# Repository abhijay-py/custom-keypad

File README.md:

# custom-keypad
Utilized KiCAD and STM32Cube to design a keypad pre-programmed with 6 specific key bindings and a volume knob. <br>
Powered by a STM32H7A3RGT6 microcontroller with Cherry MX Brown Switches and a knurled metal volume knob. <br>
Enclosed the PCB with a custom black 3D printed case to improve the appearance, saftey, and stabliity of the device. 

Used consumer and keypad hardware interface device reports to create a custom HID report that was able to send both media and regular keyboard commands to PCs. 
Created a decoder + EXTI interrupt system to properly debounce and evaluate transistions in the rotary encoder to effectively adjust volume corresponding to the end user's turning of the dial. <br>

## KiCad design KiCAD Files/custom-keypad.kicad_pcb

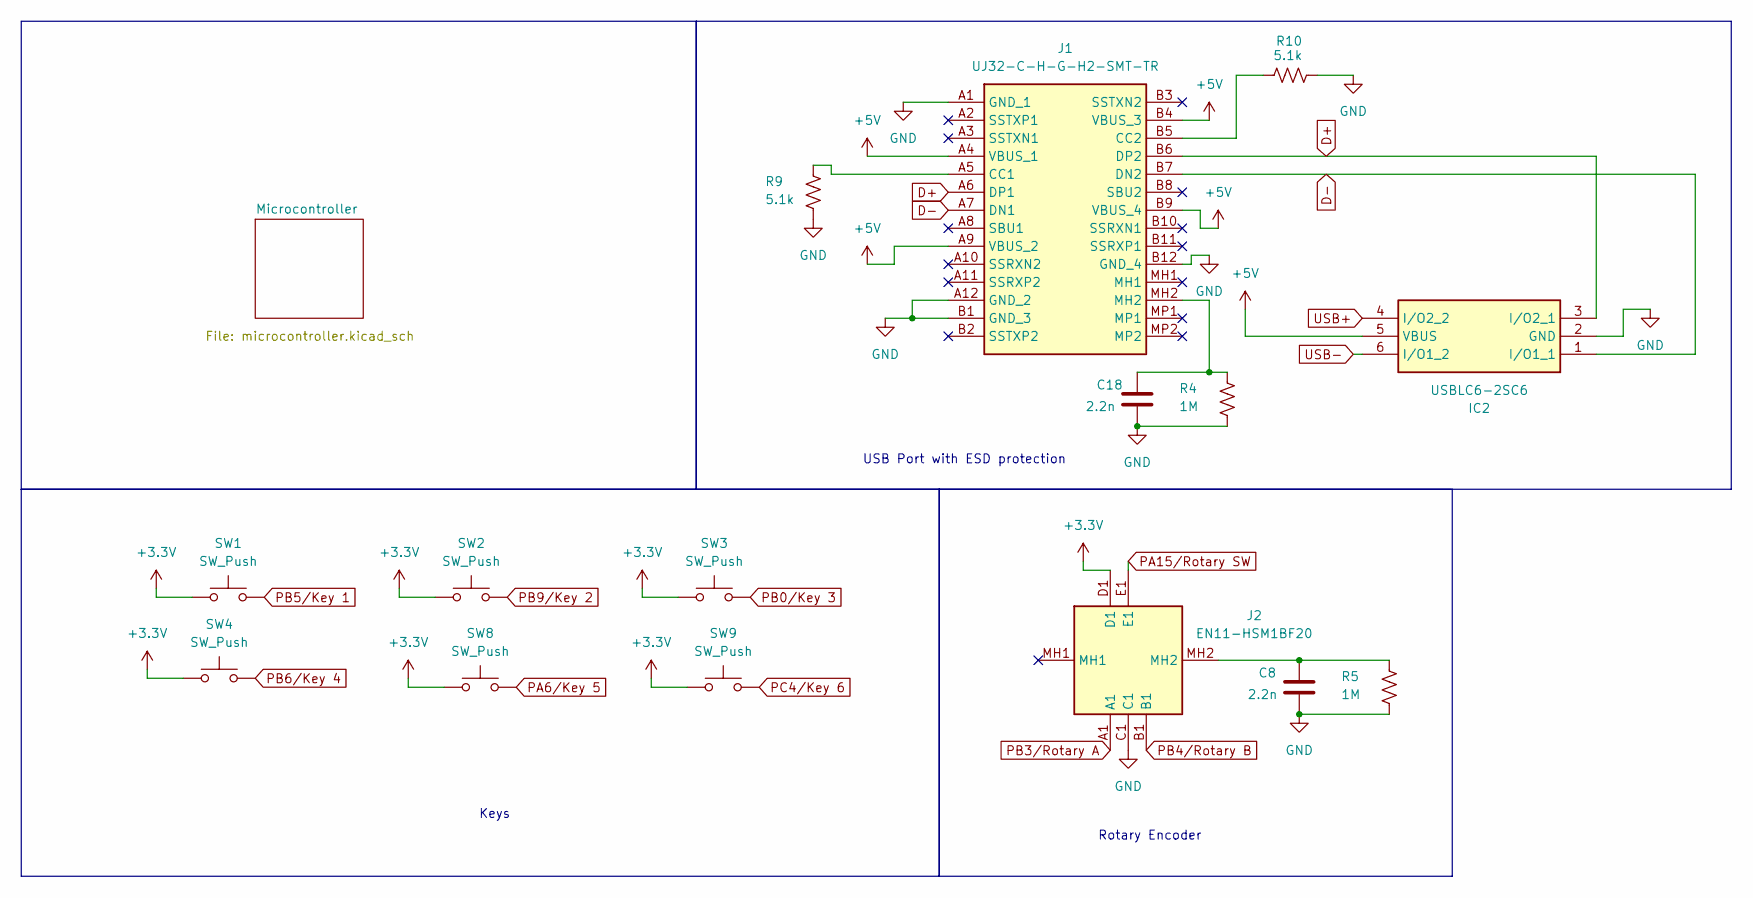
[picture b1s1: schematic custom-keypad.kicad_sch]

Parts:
C8, C18: 2.2n; C_0805_2012Metric_Pad1.18x1.45mm_HandSolder
IC2: USBLC6-2SC6; SOT95P280X145-6N; Mouser Part Number 511-USBLC6-2SC6
J1: UJ32-C-H-G-H2-SMT-TR; UJ32CHGH2SMTTR; Mouser Part Number 179-UJ32CHGH2SMTTR
J2: EN11-HSM1BF20; EN11HSM1BF20; Mouser Part Number 858-EN11-HSM1BF20
R4, R5: 1M; R_0805_2012Metric_Pad1.20x1.40mm_HandSolder
R9, R10: 5.1k; R_0805_2012Metric_Pad1.20x1.40mm_HandSolder
SW1, SW2, SW3, SW4, SW8, SW9: SW_Push; SW_MX

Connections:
+5V: IC2.5 (VBUS), J1.A4 (VBUS_1), J1.A9 (VBUS_2), J1.B4 (VBUS_3), J1.B9 (VBUS_4); also elsewhere on the board
D+: IC2.3 (I/O2_1), J1.A6 (DP1), J1.B6 (DP2)
D-: IC2.1 (I/O1_1), J1.A7 (DN1), J1.B7 (DN2)
GND: C8.2, C18.2, IC2.2 (GND), J1.A1 (GND_1), J1.A12 (GND_2), J1.B1 (GND_3), J1.B12 (GND_4), J2.C1, R4.2, R5.2, R9.2, R10.2; also elsewhere on the board
unnamed: C8.1, J2.MH2, R5.1
unnamed: C18.1, J1.MH2, R4.1
unnamed: J1.A5 (CC1), R9.1
unnamed: J1.B5 (CC2), R10.1
PA6/Key 5: SW8.2; also elsewhere on the board
PA15/Rotary SW: J2.E1; also elsewhere on the board
PB0/Key 3: SW3.2; also elsewhere on the board
PB3/Rotary A: J2.A1; also elsewhere on the board
PB4/Rotary B: J2.B1; also elsewhere on the board
PB5/Key 1: SW1.2; also elsewhere on the board
PB6/Key 4: SW4.2; also elsewhere on the board
PB9/Key 2: SW2.2; also elsewhere on the board
PC4/Key 6: SW9.2; also elsewhere on the board
USB+: IC2.4 (I/O2_2); also elsewhere on the board
USB-: IC2.6 (I/O1_2); also elsewhere on the board
VBAT: J2.D1, SW1.1, SW2.1, SW3.1, SW4.1, SW8.1, SW9.1; also elsewhere on the board

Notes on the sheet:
Keys
Rotary Encoder
USB Port with ESD protection

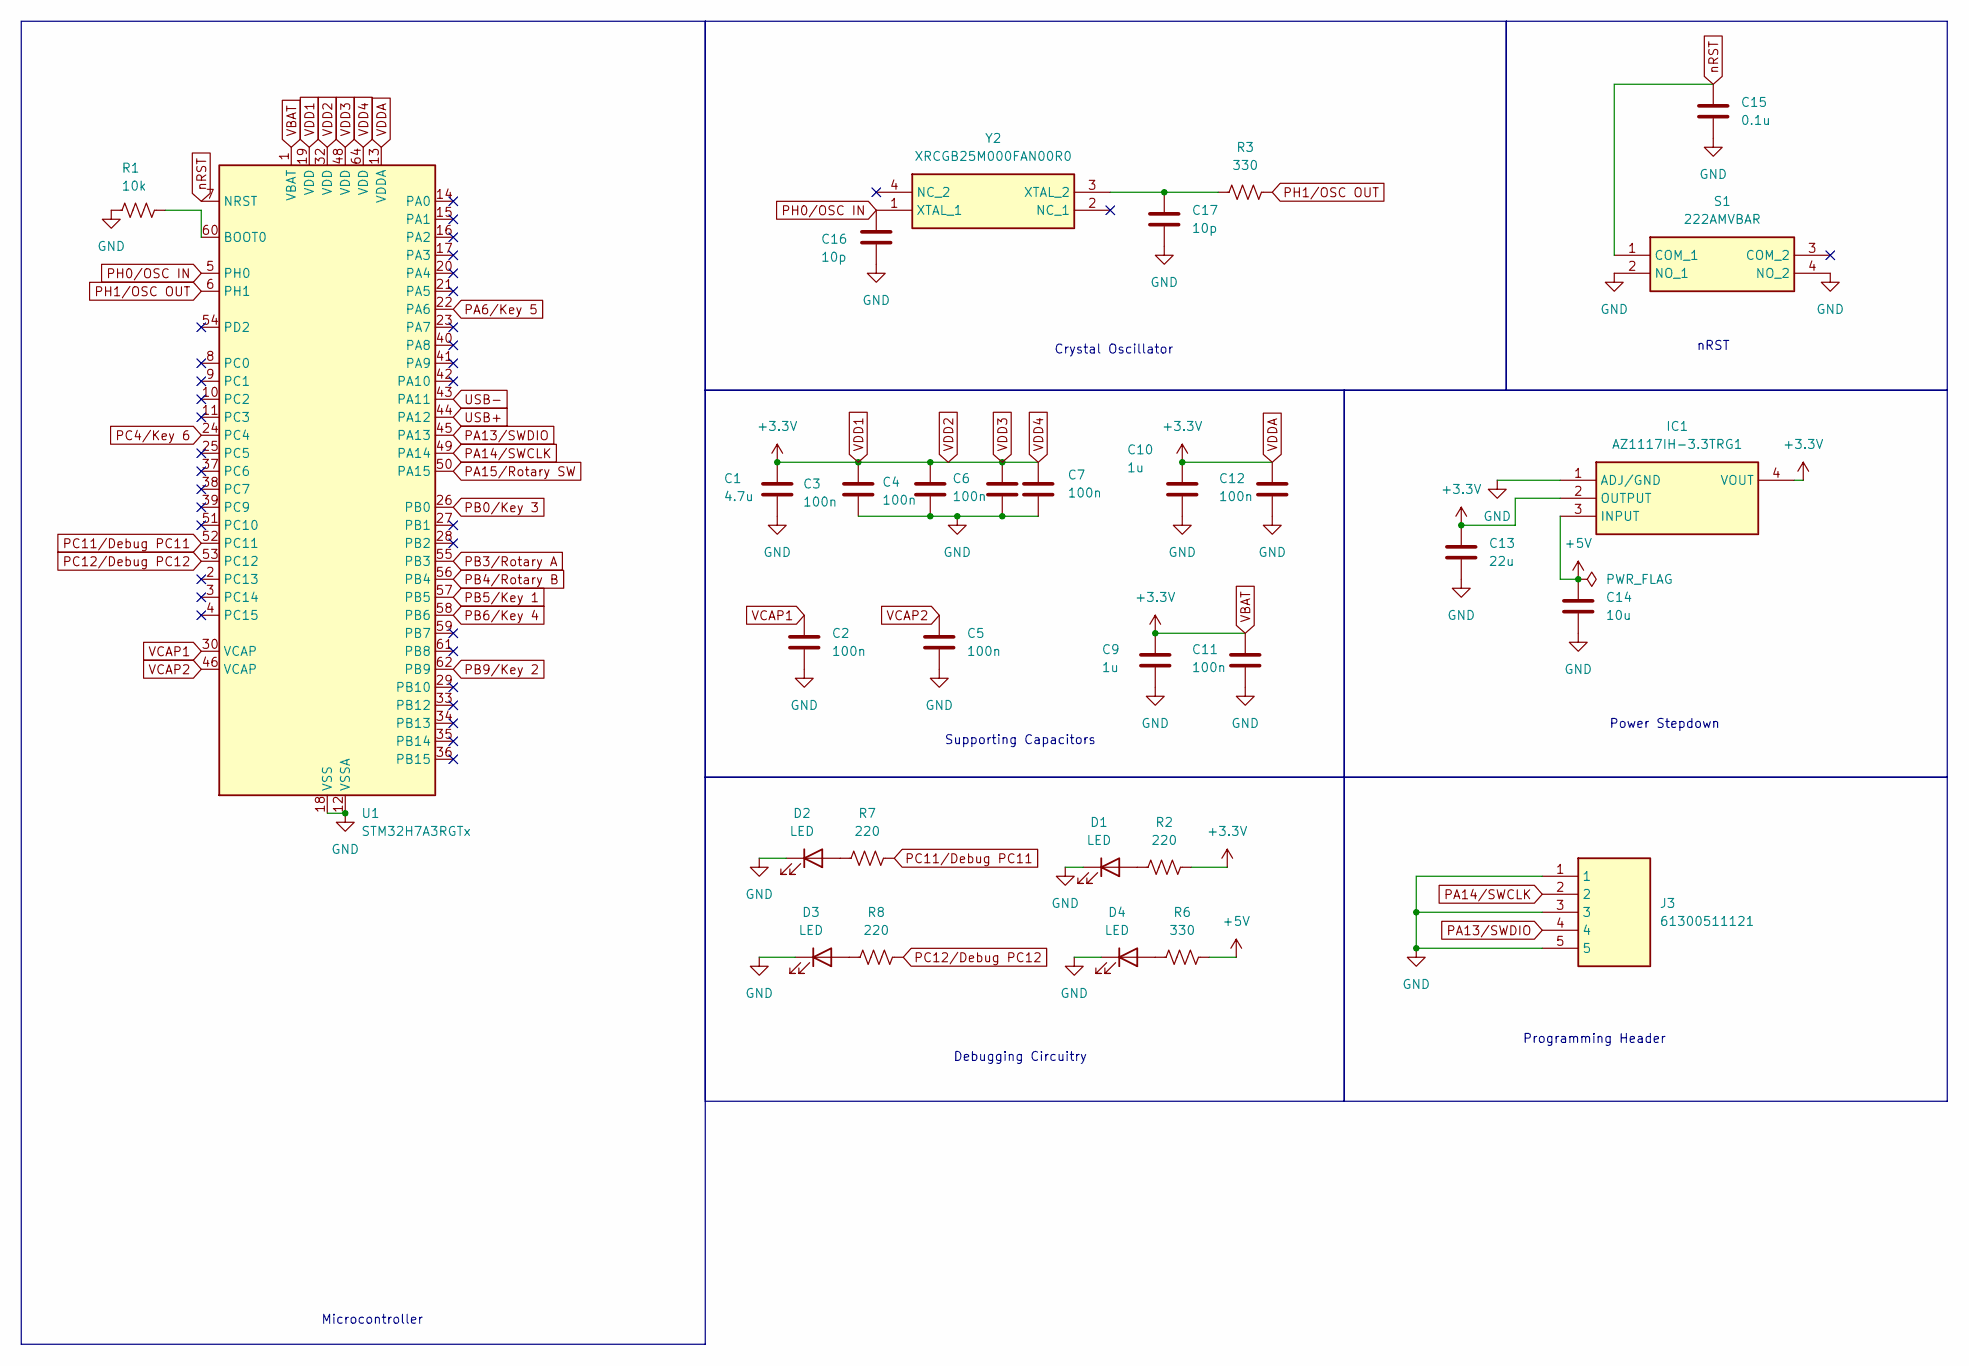
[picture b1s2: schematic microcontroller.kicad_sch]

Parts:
C1: 4.7u; C_0805_2012Metric_Pad1.18x1.45mm_HandSolder
C2, C3, C4, C5, C6, C7, C11, C12: 100n; C_0805_2012Metric_Pad1.18x1.45mm_HandSolder
C9, C10: 1u; C_0805_2012Metric_Pad1.18x1.45mm_HandSolder
C13: 22u; C_0805_2012Metric_Pad1.18x1.45mm_HandSolder
C14: 10u; C_0805_2012Metric_Pad1.18x1.45mm_HandSolder
C15: 0.1u; C_0805_2012Metric_Pad1.18x1.45mm_HandSolder
C16, C17: 10p; C_0805_2012Metric_Pad1.18x1.45mm_HandSolder
D1, D2, D3, D4: LED; LED_0805_2012Metric_Pad1.15x1.40mm_HandSolder
IC1: AZ1117IH-3.3TRG1; SOT230P700X180-4N; Mouser Part Number 621-AZ1117IH-3.3TRG1
J3: 61300511121; HDRV5W64P0X254_1X5_1270X254X854P; Mouser Part Number 710-61300511121
R1: 10k; R_0805_2012Metric_Pad1.20x1.40mm_HandSolder
R2, R7, R8: 220; R_0805_2012Metric_Pad1.20x1.40mm_HandSolder
R3, R6: 330; R_0805_2012Metric_Pad1.20x1.40mm_HandSolder
S1: 222AMVBAR; Mouser Part Number 774-222AMVBAR
U1: STM32H7A3RGTx; LQFP-64_10x10mm_P0.5mm
Y2: XRCGB25M000FAN00R0; XRCGB; Mouser Part Number 81-XRCGB25M000FAN0R0

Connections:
+5V: C14.1, IC1.3 (INPUT), R6.1; also elsewhere on the board
GND: C1.2, C2.2, C3.2, C4.2, C5.2, C6.2, C7.2, C9.2, C10.2, C11.2, C12.2, C13.2, C14.2, C15.2, C16.2, C17.2, D1.1 (K), D2.1 (K), D3.1 (K), D4.1 (K), IC1.1 (ADJ/GND), J3.1, J3.3, J3.5, R1.2, S1.2 (NO_1), S1.4 (NO_2), U1.12 (VSSA), U1.18 (VSS), U1.31 (VSS), U1.47 (VSS), U1.63 (VSS); also elsewhere on the board
unnamed: D1.2 (A), R2.2
unnamed: D2.2 (A), R7.2
unnamed: D3.2 (A), R8.2
unnamed: D4.2 (A), R6.2
unnamed: R1.1, U1.60 (BOOT0)
unnamed: C17.1, R3.1, Y2.3 (XTAL_2)
PA6/Key 5: U1.22 (PA6); also elsewhere on the board
PA13/SWDIO: J3.4, U1.45 (PA13)
PA14/SWCLK: J3.2, U1.49 (PA14)
PA15/Rotary SW: U1.50 (PA15); also elsewhere on the board
PB0/Key 3: U1.26 (PB0); also elsewhere on the board
PB3/Rotary A: U1.55 (PB3); also elsewhere on the board
PB4/Rotary B: U1.56 (PB4); also elsewhere on the board
PB5/Key 1: U1.57 (PB5); also elsewhere on the board
PB6/Key 4: U1.58 (PB6); also elsewhere on the board
PB9/Key 2: U1.62 (PB9); also elsewhere on the board
PC4/Key 6: U1.24 (PC4); also elsewhere on the board
PC11/Debug PC11: R7.1, U1.52 (PC11)
PC12/Debug PC12: R8.1, U1.53 (PC12)
PH0/OSC IN: C16.1, U1.5 (PH0), Y2.1 (XTAL_1)
PH1/OSC OUT: R3.2, U1.6 (PH1)
USB+: U1.44 (PA12); also elsewhere on the board
USB-: U1.43 (PA11); also elsewhere on the board
VBAT: C1.1, C3.1, C4.1, C6.1, C7.1, C9.1, C10.1, C11.1, C12.1, C13.1, IC1.2 (OUTPUT), IC1.4 (VOUT), R2.1, U1.1 (VBAT), U1.13 (VDDA), U1.19 (VDD), U1.32 (VDD), U1.48 (VDD), U1.64 (VDD); also elsewhere on the board
VCAP1: C2.1, U1.30 (VCAP)
VCAP2: C5.1, U1.46 (VCAP)
nRST: C15.1, S1.1 (COM_1), U1.7 (NRST)

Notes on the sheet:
Power Stepdown
Debugging Circuitry
nRST
Programming Header
Crystal Oscillator
Microcontroller
Supporting Capacitors

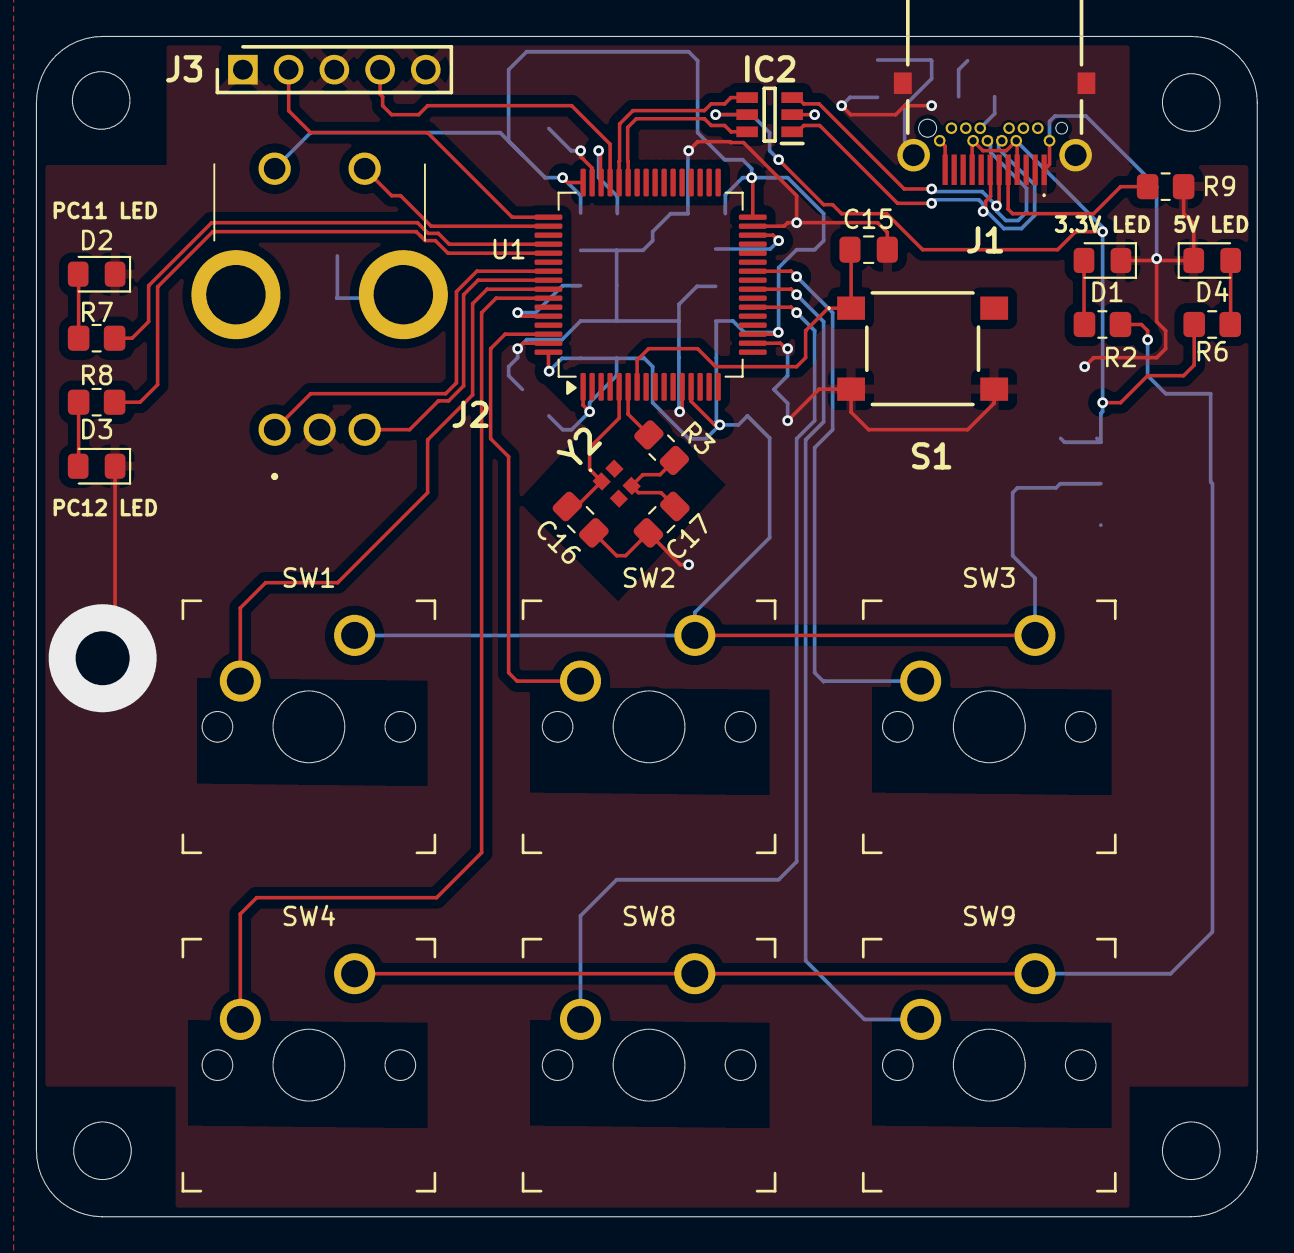
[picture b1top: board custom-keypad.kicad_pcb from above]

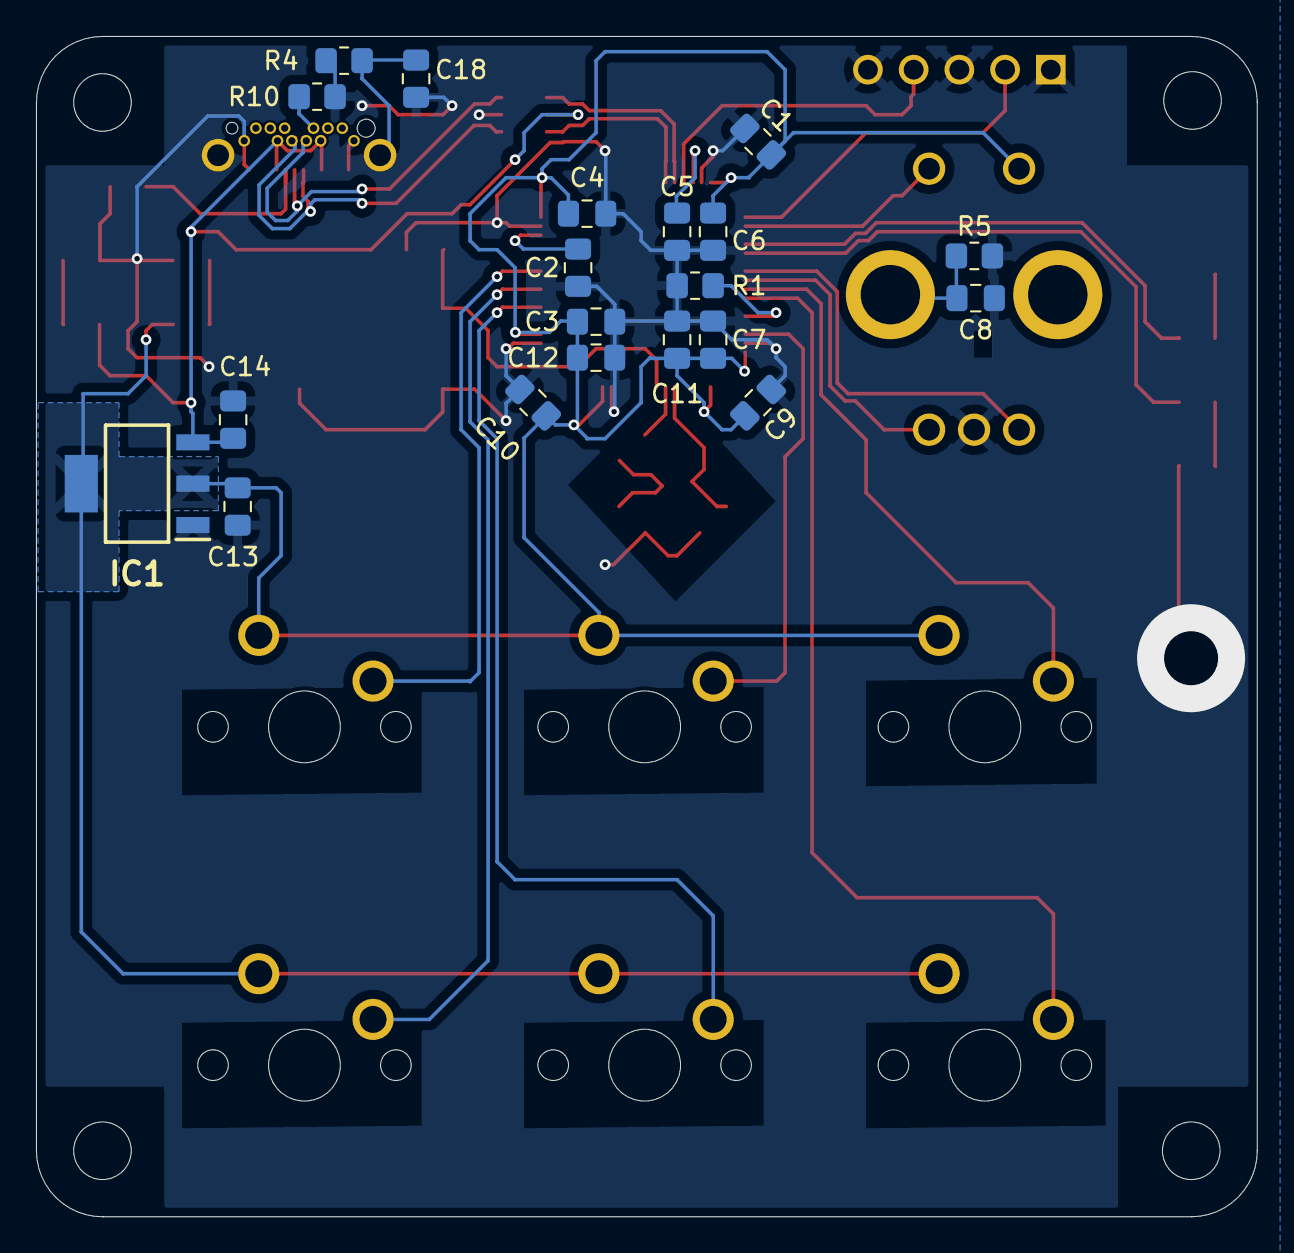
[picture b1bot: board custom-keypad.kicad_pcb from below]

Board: 2 copper layers, 67.8 x 65.6 mm, 46 parts (20 on the bottom side), 35 nets.

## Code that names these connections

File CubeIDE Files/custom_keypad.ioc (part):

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Mcu.Name=STM32H7A3R(G-I)Tx
Mcu.Package=LQFP64
Mcu.UserName=STM32H7A3RGTx
PA11.Mode=Device_Only_FS
PA11.Signal=USB_OTG_HS_DM
PA12.Mode=Device_Only_FS
PA12.Signal=USB_OTG_HS_DP
PA13.Mode=Serial_Wire
PA13.Signal=DEBUG_JTMS-SWDIO
PA14.Mode=Serial_Wire
PA14.Signal=DEBUG_JTCK-SWCLK
PA15.GPIOParameters=GPIO_PuPd
PA15.GPIO_PuPd=GPIO_PULLDOWN
PA15.Signal=GPIO_Input
PA6.GPIOParameters=GPIO_PuPd
PA6.GPIO_PuPd=GPIO_PULLDOWN
PA6.Signal=GPIO_Input
PB0.GPIOParameters=GPIO_PuPd
PB0.GPIO_PuPd=GPIO_PULLDOWN
PB0.Signal=GPIO_Input
PB3.GPIOParameters=GPIO_PuPd,GPIO_ModeDefaultEXTI
PB3.GPIO_ModeDefaultEXTI=GPIO_MODE_IT_RISING_FALLING
PB3.GPIO_PuPd=GPIO_PULLUP
PB3.Signal=GPXTI3
PB4.GPIOParameters=GPIO_PuPd,GPIO_ModeDefaultEXTI
PB4.GPIO_ModeDefaultEXTI=GPIO_MODE_IT_RISING_FALLING
PB4.GPIO_PuPd=GPIO_PULLUP
PB4.Signal=GPXTI4
PB5.GPIOParameters=GPIO_PuPd
PB5.GPIO_PuPd=GPIO_PULLDOWN
PB5.Signal=GPIO_Input
PB6.GPIOParameters=GPIO_PuPd
PB6.GPIO_PuPd=GPIO_PULLDOWN
PB6.Signal=GPIO_Input
PB9.GPIOParameters=GPIO_PuPd
PB9.GPIO_PuPd=GPIO_PULLDOWN
PB9.Signal=GPIO_Input
PC11.Signal=GPIO_Output
PC12.Signal=GPIO_Output
PC4.GPIOParameters=GPIO_PuPd
PC4.GPIO_PuPd=GPIO_PULLDOWN
PC4.Signal=GPIO_Input
PH0-OSC_IN.Mode=HSE-External-Oscillator
PH0-OSC_IN.Signal=RCC_OSC_IN
PH1-OSC_OUT.Mode=HSE-External-Oscillator
PH1-OSC_OUT.Signal=RCC_OSC_OUT
RCC.HSE_VALUE=25000000
RCC.SYSCLKFreq_VALUE=64000000
board=custom

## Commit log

2025-04-11 initial schematic files
2025-04-11 changed out microcontroller
    Might add in a bit of debug circuitry + button leds will see tmmrw
2025-04-11 initial schematic and pcb designs
2025-04-11 improved PCB design and added debugging circuitry
2025-04-11 fixed some drc issues and updated pcb
2025-04-11 adjusted placement of oscillator
2025-04-12 finished pcb and diagram, need to double check before producing
2025-04-12 committing unsaved changes
2025-04-12 tweaked PCB to isolate USB a bit more
2025-04-14 tweaked 3d model + added drill files for jlc
2025-04-15 initialized keyboard + added keyboard constants
    need to check what kind of timer system needs to be implemented to ensure volume status + all 6 keys can be communicated in parallel or close to parallel
2025-04-15 updated kicad file status
2025-04-22 Started working on firmware, ran into issues with USB
2025-04-23 updated files for remaking pcb assembly
2025-06-01 adjusted programming header location to provide more space to dial
2025-06-01 closed kicad
2025-07-03 added key functionality, no media/knob functions
2025-07-03 created hotkey setup with f13+ keys and implemented play/pause + volume mute
2025-07-03 adjusted delay
2025-07-04 finished volume +/-, need to brush up functionality
2025-07-04 added psuedo-debouncing for play/skip/rewind buttons
2025-07-05 removed irrelevant code
2025-07-05 retrieved older pcb files that were manufactured
2025-07-09 got rotary encoder working, hotkey bugging
    figure out report system
2025-07-09 finished consumer commands
2025-07-09 retuned timing delays
2025-07-11 finalized case (adjustments can be made)
2025-07-17 Finished v1 3d model + software
2025-07-20 started adjusting changes for 65% keyboard
2025-07-20 Revert "started adjusting changes for 65% keyboard"
    This reverts commit 731512e8e337a2e6137dad3074b859df4f5567bd.
2025-07-20 updated with keyboard 65%
2025-07-21 added step files for use in production outside of 3d printing
2025-08-14 added image of device
2025-08-14 Update README.md with picture
2025-08-14 removed image of device as it exists in readme
